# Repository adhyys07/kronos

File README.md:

## Kronos
Kronos is a split gaming keyboard with RGB keys support powered by XIAO-nRF52840-SMD, it uses two of the xioa board for the left and right side and it's a complete wireless keyboard that coan be connected to your devices easily. I am also gonna try to make a dedicated firmware + software for the keyboard although I am not sure for it but I would really like to make one.

## Some Images and Technical Things

## Bill Of Material (BOM)

| Item Name | Quantity | Link | Total Cost 
|----------|----------|----------|----------|
| Seeed XIAO nRF52840 | 2 | [Board Link](https://robocraze.com/products/seeed-studio-xiao-nrf52840-development-board-supports-bluetooth-5-0?variant=47769216516320) | $ 25 |
| | Row 2, C2 | Row 2, C3 |  Row 1, C3 |

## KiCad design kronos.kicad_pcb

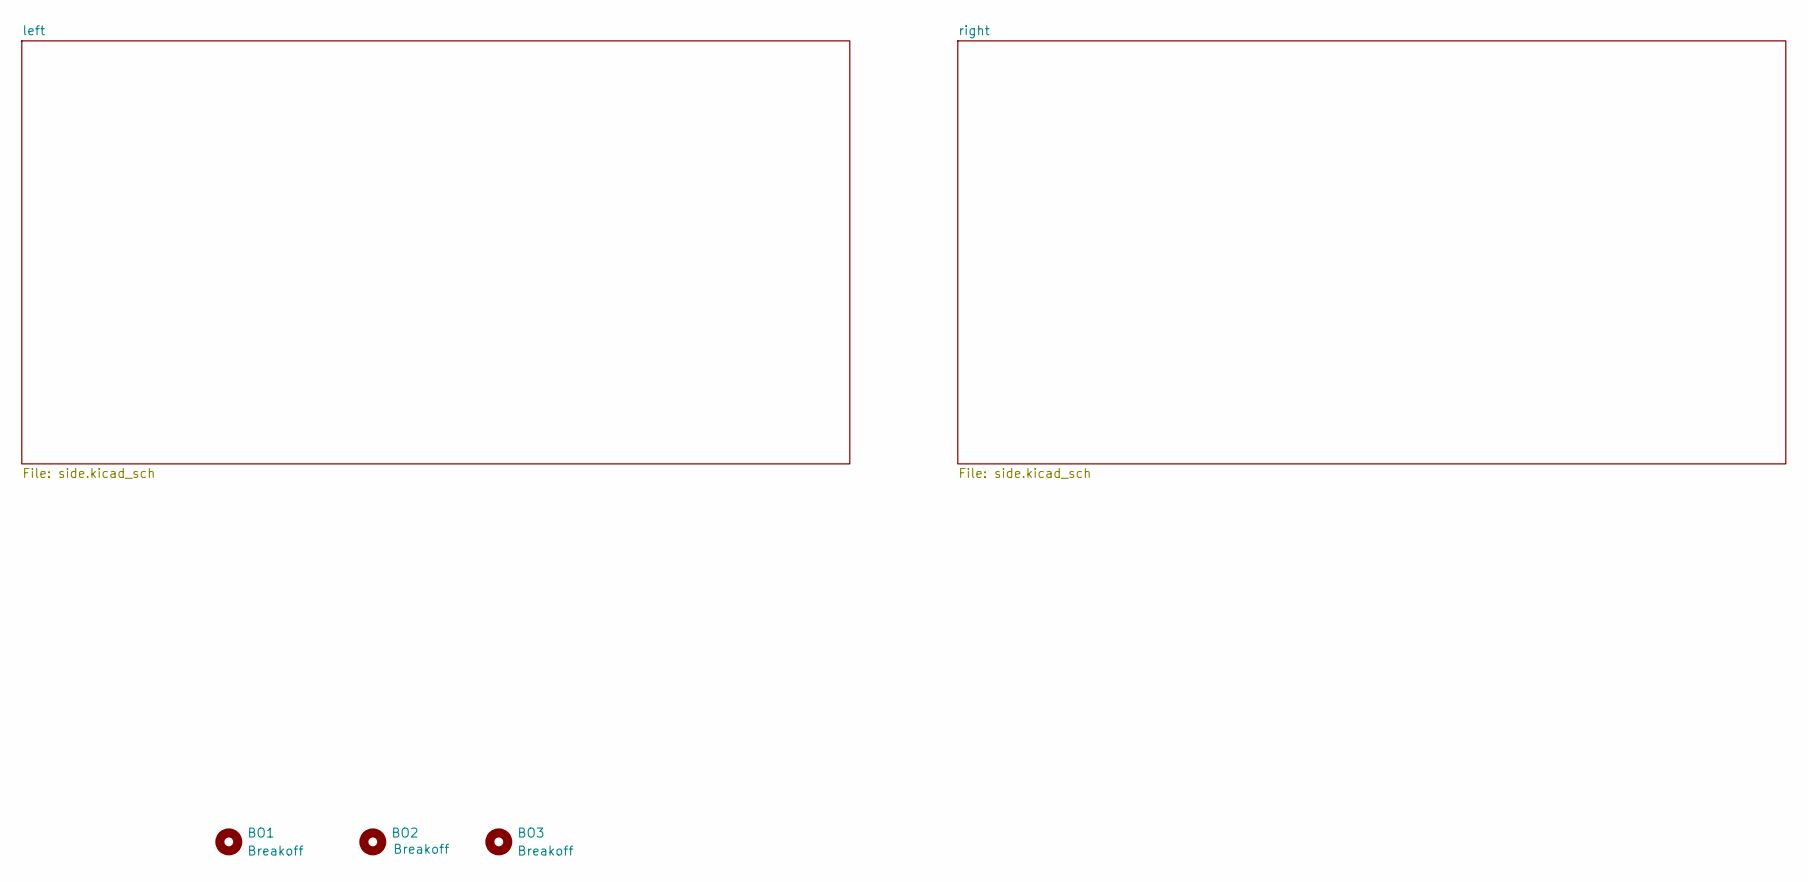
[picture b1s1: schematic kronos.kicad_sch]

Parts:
BO1, BO2, BO3: Breakoff

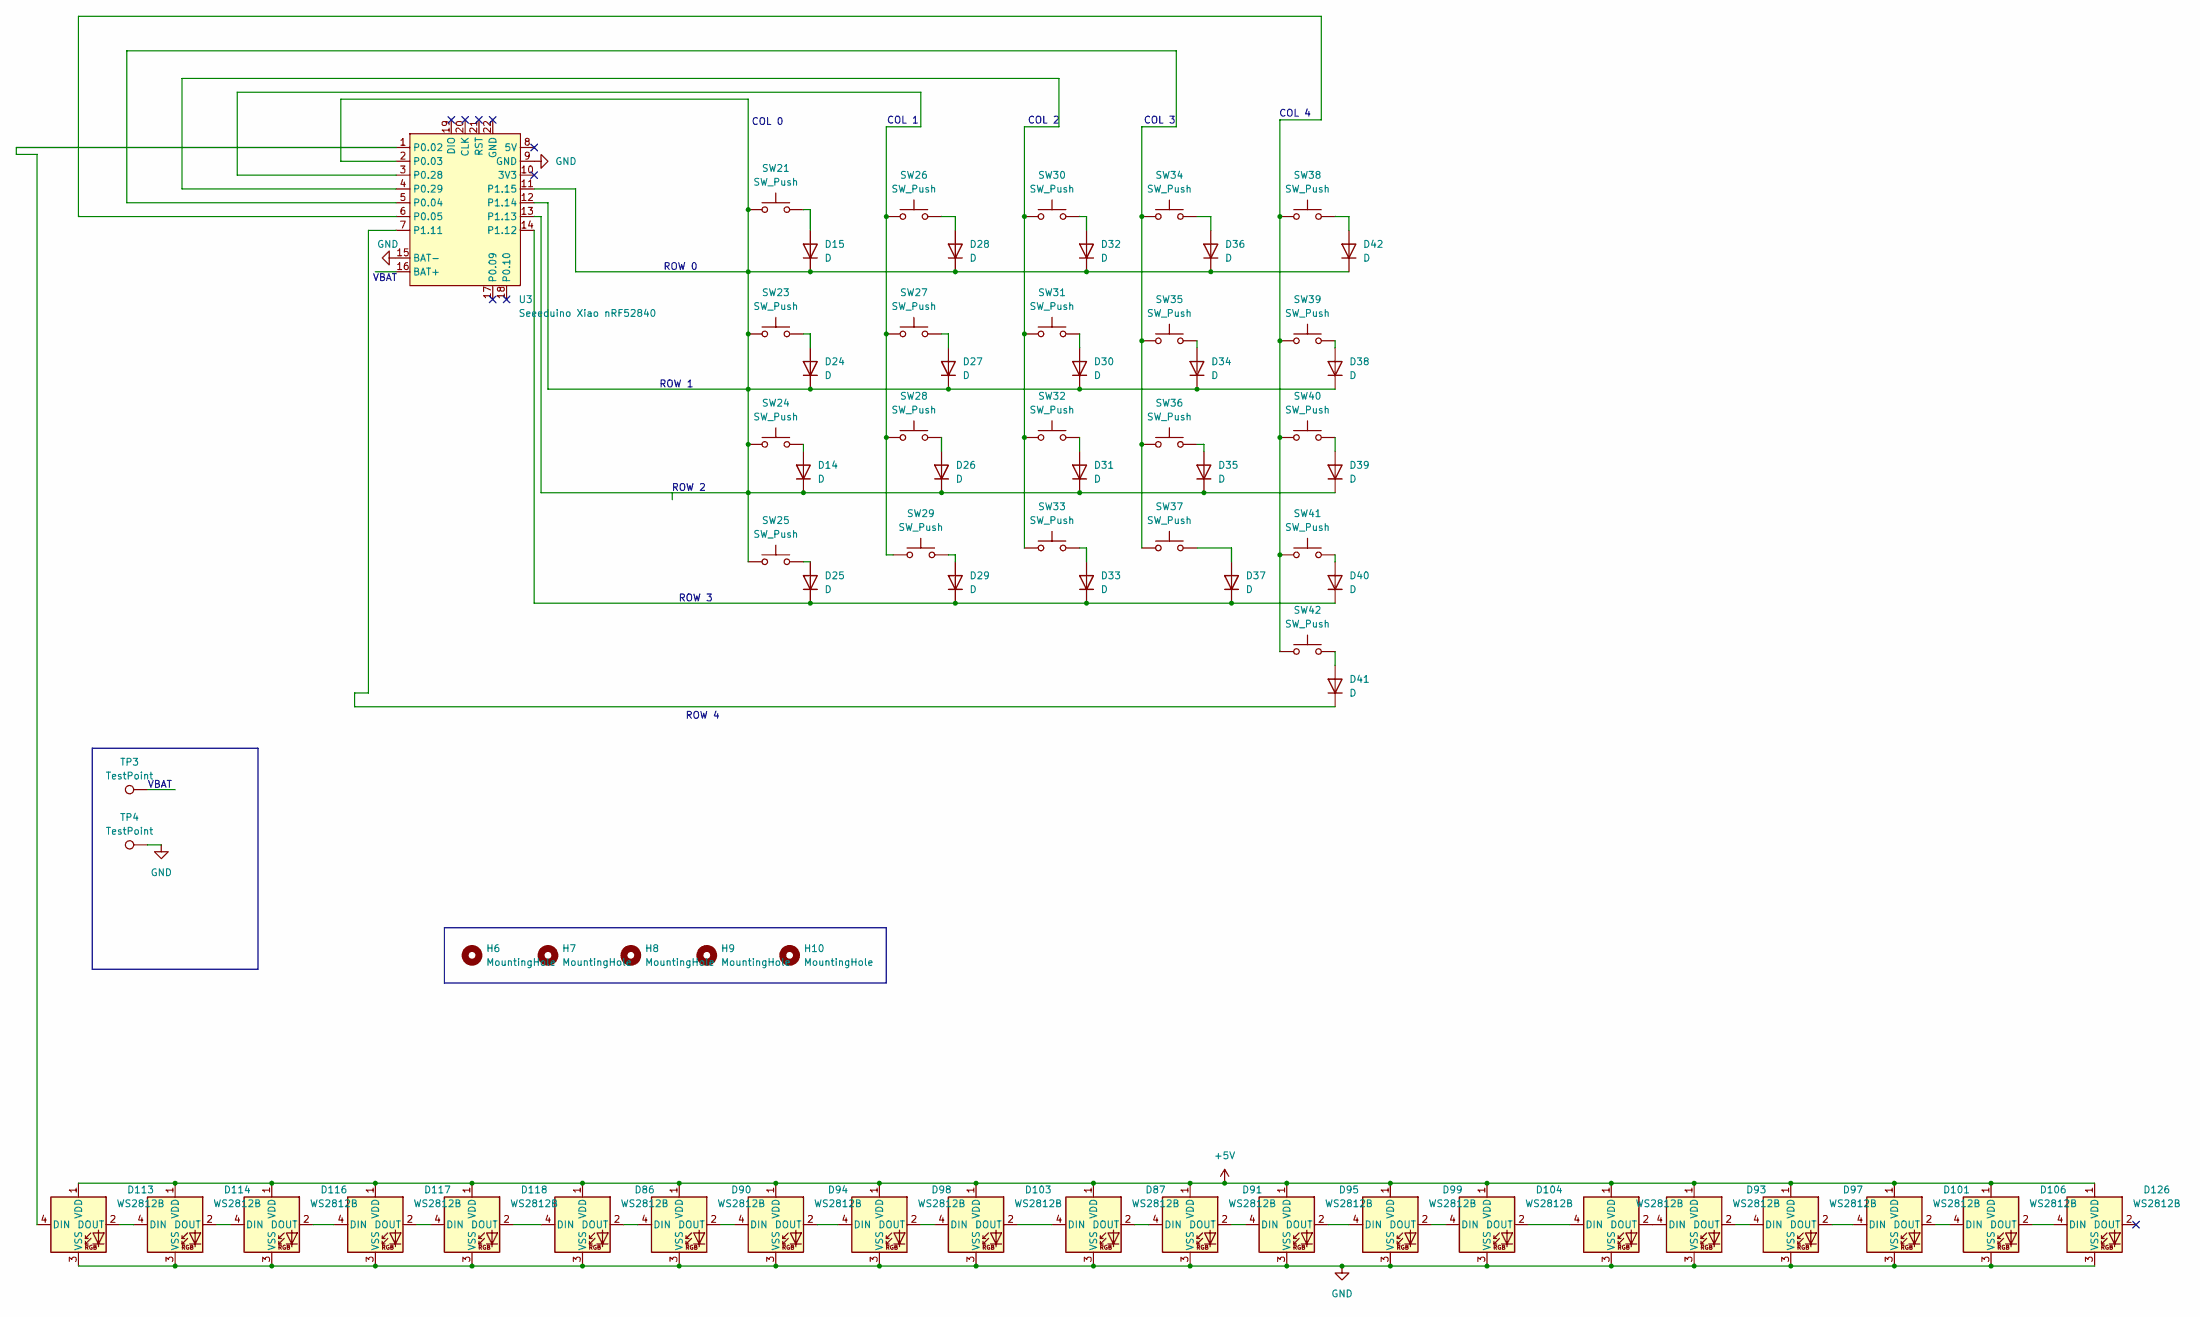
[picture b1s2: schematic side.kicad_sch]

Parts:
D14, D15, D24, D25, D26, D27, D28, D29, D30, D31, D32, D33, D34, D35, D36, D37, D38, D39, D40, D41, D42: D; D_SOD-123
D86, D87, D89, D90, D91, D93, D94, D95, D97, D98, D99, D101, D103, D104, D106, D113, D114, D116, D117, D118, D126: WS2812B; LED_WS2812B_PLCC4_5.0x5.0mm_P3.2mm
H6, H7, H8, H9, H10: MountingHole; mouse-bite-5mm-slot
SW21, SW23, SW24, SW25, SW26, SW27, SW28, SW29, SW30, SW31, SW32, SW33, SW34, SW35, SW36, SW37, SW38, SW39, SW40, SW41, SW42: SW_Push; SW_MX_HS_KS-2P02B01-01_1u
TP3, TP4: TestPoint; TestPoint_Pad_D2.0mm
U3: Seeeduino Xiao nRF52840; Xiao_nRF52840_ACH

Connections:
+5V: D86.1 (VDD), D87.1 (VDD), D89.1 (VDD), D90.1 (VDD), D91.1 (VDD), D93.1 (VDD), D94.1 (VDD), D95.1 (VDD), D97.1 (VDD), D98.1 (VDD), D99.1 (VDD), D101.1 (VDD), D103.1 (VDD), D104.1 (VDD), D106.1 (VDD), D113.1 (VDD), D114.1 (VDD), D116.1 (VDD), D117.1 (VDD), D118.1 (VDD), D126.1 (VDD); also elsewhere on the board
GND: D86.3 (VSS), D87.3 (VSS), D89.3 (VSS), D90.3 (VSS), D91.3 (VSS), D93.3 (VSS), D94.3 (VSS), D95.3 (VSS), D97.3 (VSS), D98.3 (VSS), D99.3 (VSS), D101.3 (VSS), D103.3 (VSS), D104.3 (VSS), D106.3 (VSS), D113.3 (VSS), D114.3 (VSS), D116.3 (VSS), D117.3 (VSS), D118.3 (VSS), D126.3 (VSS), TP4.1 (1_1), U3.9 (GND), U3.15 (BAT-); also elsewhere on the board
unnamed: D14.2 (A), SW24.2
unnamed: D14.1 (K), D15.1 (K), D24.1 (K), D26.1 (K), D27.1 (K), D28.1 (K), D30.1 (K), D31.1 (K), D32.1 (K), D34.1 (K), D35.1 (K), D36.1 (K), D38.1 (K), D39.1 (K), D42.1 (K), SW21.1, SW23.1, SW24.1, SW25.1, U3.2 (P0.03), U3.11 (P1.15), U3.12 (P1.14), U3.13 (P1.13)
unnamed: D15.2 (A), SW21.2
unnamed: D24.2 (A), SW23.2
unnamed: D25.2 (A), SW25.2
unnamed: D25.1 (K), D29.1 (K), D33.1 (K), D37.1 (K), D40.1 (K), U3.14 (P1.12)
unnamed: D26.2 (A), SW28.2
unnamed: D27.2 (A), SW27.2
unnamed: D28.2 (A), SW26.2
unnamed: D29.2 (A), SW29.2
unnamed: D30.2 (A), SW31.2
unnamed: D31.2 (A), SW32.2
unnamed: D32.2 (A), SW30.2
unnamed: D33.2 (A), SW33.2
unnamed: D34.2 (A), SW35.2
unnamed: D35.2 (A), SW36.2
unnamed: D36.2 (A), SW34.2
unnamed: D37.2 (A), SW37.2
unnamed: D38.2 (A), SW39.2
unnamed: D39.2 (A), SW40.2
unnamed: D40.2 (A), SW41.2
unnamed: D41.2 (A), SW42.2
unnamed: D41.1 (K), U3.7 (P1.11)
unnamed: D42.2 (A), SW38.2
unnamed: D86.2 (DOUT), D90.4 (DIN)
unnamed: D87.2 (DOUT), D91.4 (DIN)
unnamed: D89.2 (DOUT), D93.4 (DIN)
unnamed: D90.2 (DOUT), D94.4 (DIN)
unnamed: D91.2 (DOUT), D95.4 (DIN)
unnamed: D93.2 (DOUT), D97.4 (DIN)
unnamed: D94.2 (DOUT), D98.4 (DIN)
unnamed: D95.2 (DOUT), D99.4 (DIN)
unnamed: D97.2 (DOUT), D101.4 (DIN)
unnamed: D101.2 (DOUT), D106.4 (DIN)
unnamed: D98.2 (DOUT), D103.4 (DIN)
unnamed: D87.4 (DIN), D103.2 (DOUT)
unnamed: D99.2 (DOUT), D104.4 (DIN)
unnamed: D89.4 (DIN), D104.2 (DOUT)
unnamed: D106.2 (DOUT), D126.4 (DIN)
unnamed: D113.4 (DIN), U3.1 (P0.02)
unnamed: D113.2 (DOUT), D114.4 (DIN)
unnamed: D114.2 (DOUT), D116.4 (DIN)
unnamed: D116.2 (DOUT), D117.4 (DIN)
unnamed: D117.2 (DOUT), D118.4 (DIN)
unnamed: D86.4 (DIN), D118.2 (DOUT)
unnamed: SW34.1, SW35.1, SW36.1, SW37.1, U3.5 (P0.04)
unnamed: SW38.1, SW39.1, SW40.1, SW41.1, SW42.1, U3.6 (P0.05)
unnamed: SW26.1, SW27.1, SW28.1, SW29.1, U3.3 (P0.28)
unnamed: SW30.1, SW31.1, SW32.1, SW33.1, U3.4 (P0.29)

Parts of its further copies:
D1, D2, D3, D4, D5, D6, D7, D8, D9, D10, D11, D12, D13, D16, D17, D18, D19, D20, D21, D22, D23: D; D_SOD-123
D88, D92, D96, D100, D102, D105, D107, D108, D109, D110, D111, D112, D115, D119, D120, D121, D122, D123, D124, D125, D127: WS2812B; LED_WS2812B_PLCC4_5.0x5.0mm_P3.2mm
H1, H2, H3, H4, H5: MountingHole; mouse-bite-5mm-slot
SW1, SW2, SW3, SW4, SW5, SW6, SW7, SW8, SW9, SW10, SW11, SW12, SW13, SW14, SW15, SW16, SW17, SW18, SW19, SW20, SW22: SW_Push; SW_MX_HS_KS-2P02B01-01_1u
TP1, TP2: TestPoint; TestPoint_Pad_D2.0mm
U4: Seeeduino Xiao nRF52840; Xiao_nRF52840_ACH

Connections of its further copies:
+5V: D88.1 (VDD), D92.1 (VDD), D96.1 (VDD), D100.1 (VDD), D102.1 (VDD), D105.1 (VDD), D107.1 (VDD), D108.1 (VDD), D109.1 (VDD), D110.1 (VDD), D111.1 (VDD), D112.1 (VDD), D115.1 (VDD), D119.1 (VDD), D120.1 (VDD), D121.1 (VDD), D122.1 (VDD), D123.1 (VDD), D124.1 (VDD), D125.1 (VDD), D127.1 (VDD); also elsewhere on the board
GND: D88.3 (VSS), D92.3 (VSS), D96.3 (VSS), D100.3 (VSS), D102.3 (VSS), D105.3 (VSS), D107.3 (VSS), D108.3 (VSS), D109.3 (VSS), D110.3 (VSS), D111.3 (VSS), D112.3 (VSS), D115.3 (VSS), D119.3 (VSS), D120.3 (VSS), D121.3 (VSS), D122.3 (VSS), D123.3 (VSS), D124.3 (VSS), D125.3 (VSS), D127.3 (VSS), TP2.1 (1_1), U4.9 (GND), U4.15 (BAT-); also elsewhere on the board
unnamed: D1.2 (A), SW3.2
unnamed: D1.1 (K), D2.1 (K), D3.1 (K), D5.1 (K), D6.1 (K), D7.1 (K), D9.1 (K), D10.1 (K), D11.1 (K), D13.1 (K), D16.1 (K), D17.1 (K), D19.1 (K), D20.1 (K), D23.1 (K), SW1.1, SW2.1, SW3.1, SW4.1, U4.2 (P0.03), U4.11 (P1.15), U4.12 (P1.14), U4.13 (P1.13)
unnamed: D2.2 (A), SW1.2
unnamed: D3.2 (A), SW2.2
unnamed: D4.2 (A), SW4.2
unnamed: D5.2 (A), SW7.2
unnamed: D6.2 (A), SW6.2
unnamed: D7.2 (A), SW5.2
unnamed: D8.2 (A), SW8.2
unnamed: D9.2 (A), SW10.2
unnamed: D10.2 (A), SW11.2
unnamed: D11.2 (A), SW9.2
unnamed: D12.2 (A), SW12.2
unnamed: D4.1 (K), D8.1 (K), D12.1 (K), D18.1 (K), D21.1 (K), U4.14 (P1.12)
unnamed: D13.2 (A), SW14.2
unnamed: D16.2 (A), SW15.2
unnamed: D17.2 (A), SW13.2
unnamed: D18.2 (A), SW16.2
unnamed: D19.2 (A), SW18.2
unnamed: D20.2 (A), SW19.2
unnamed: D21.2 (A), SW20.2
unnamed: D22.2 (A), SW22.2
unnamed: D22.1 (K), U4.7 (P1.11)
unnamed: D23.2 (A), SW17.2
unnamed: D88.2 (DOUT), D92.4 (DIN)
unnamed: D92.2 (DOUT), D96.4 (DIN)
unnamed: D96.2 (DOUT), D100.4 (DIN)
unnamed: D100.2 (DOUT), D105.4 (DIN)
unnamed: D102.4 (DIN), D105.2 (DOUT)
unnamed: D102.2 (DOUT), D108.4 (DIN)
unnamed: D107.4 (DIN), D125.2 (DOUT)
unnamed: D107.2 (DOUT), D111.4 (DIN)
unnamed: D108.2 (DOUT), D109.4 (DIN)
unnamed: D109.2 (DOUT), D110.4 (DIN)
unnamed: D110.2 (DOUT), D112.4 (DIN)
unnamed: D111.2 (DOUT), D115.4 (DIN)
unnamed: D112.2 (DOUT), D127.4 (DIN)
unnamed: D115.2 (DOUT), D119.4 (DIN)
unnamed: D119.2 (DOUT), D124.4 (DIN)
unnamed: D120.4 (DIN), U4.1 (P0.02)
unnamed: D120.2 (DOUT), D121.4 (DIN)
unnamed: D121.2 (DOUT), D122.4 (DIN)
unnamed: D122.2 (DOUT), D123.4 (DIN)
unnamed: D123.2 (DOUT), D125.4 (DIN)
unnamed: D88.4 (DIN), D124.2 (DOUT)
unnamed: SW13.1, SW14.1, SW15.1, SW16.1, U4.5 (P0.04)
unnamed: SW17.1, SW18.1, SW19.1, SW20.1, SW22.1, U4.6 (P0.05)
unnamed: SW5.1, SW6.1, SW7.1, SW8.1, U4.3 (P0.28)
unnamed: SW9.1, SW10.1, SW11.1, SW12.1, U4.4 (P0.29)

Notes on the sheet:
COL 0
COL 3
COL 4
COL 2
VBAT
ROW 2
ROW 3
ROW 1
VBAT
COL 1
ROW 4
ROW 0

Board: 2 copper layers, 142 parts (84 on the bottom side), 100 nets, no tracks yet.

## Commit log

2026-05-01 Rename schematic halves, update sheets and backups
    Rename rightside.kicad_sch -> half.kicad_sch and lefthalf.kicad_sch -> side.kicad_sch; update sheet references, UUIDs, sheetfile names and sheet positions in kronos.kicad_sch and kronos.kicad_pro. Ma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
2026-05-01 Update README with project details and BOM
    Added project description and Bill of Material section.
2026-05-01 Update kronos PCB and add backups
    Add 11 kronos backup archives to kronos-backups/ and update kronos.kicad_pcb with expanded PCB data (layers, setup, footprints, pads and components). Also update project files kronos.kicad_prl, krono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
2026-05-04 PCB akmost done
    PCB added; scheme update; blah blah
